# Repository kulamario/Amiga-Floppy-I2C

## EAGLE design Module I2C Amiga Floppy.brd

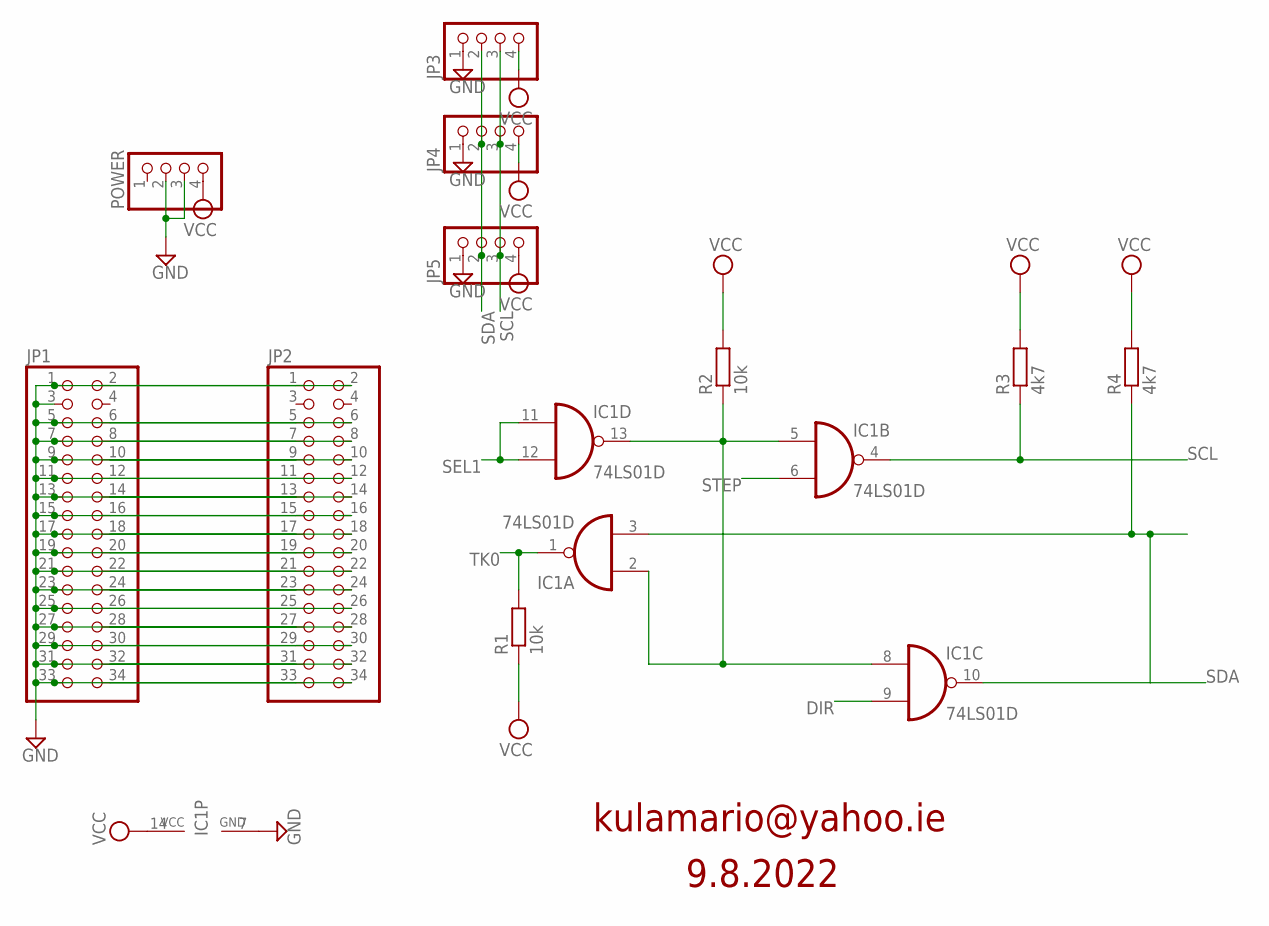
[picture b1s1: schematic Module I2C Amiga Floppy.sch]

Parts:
IC1: 74LS01D; SO14
JP1, JP2: PINHD-2X17; 2X17
JP3, JP4, JP5: PINHD-1X4; 1X04
POWER: PINHD-1X4; 1X04
R1, R2: 10k; R0805
R3, R4: 4k7; R0805

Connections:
DIR: IC1.9 (I1), JP1.18, JP2.18
GND: IC1.7 (GND), JP1.1, JP1.3, JP1.5, JP1.7, JP1.9, JP1.11, JP1.13, JP1.15, JP1.17, JP1.19, JP1.21, JP1.23, JP1.25, JP1.27, JP1.29, JP1.31, JP1.33, JP2.1, JP2.5, JP2.7, JP2.9, JP2.11, JP2.13, JP2.15, JP2.17, JP2.19, JP2.21, JP2.23, JP2.25, JP2.27, JP2.29, JP2.31, JP2.33, JP3.1, JP4.1, JP5.1, POWER.2, POWER.3
unnamed: IC1.2 (I0), IC1.5 (I0), IC1.8 (I0), IC1.13 (O), R2.1
unnamed: JP1.2, JP2.2
unnamed: JP1.6, JP2.6
unnamed: JP1.8, JP2.8
unnamed: JP1.10, JP2.10
unnamed: JP1.14, JP2.14
unnamed: JP1.16, JP2.16
unnamed: JP1.22, JP2.22
unnamed: JP1.24, JP2.24
unnamed: JP1.28, JP2.28
unnamed: JP1.30, JP2.30
unnamed: JP1.32, JP2.32
unnamed: JP1.34, JP2.34
SCL: IC1.4 (O), JP3.3, JP4.3, JP5.3, R3.1
SDA: IC1.3 (I1), IC1.10 (O), JP3.2, JP4.2, JP5.2, R4.1
SEL1: IC1.11 (I0), IC1.12 (I1), JP1.12, JP2.12
STEP: IC1.6 (I1), JP1.20, JP2.20
TK0: IC1.1 (O), JP1.26, JP2.26, R1.2
VCC: IC1.14 (VCC), JP3.4, JP4.4, JP5.4, POWER.4, R1.1, R2.2, R3.2, R4.2

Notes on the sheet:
kulamario@yahoo.ie
9.8.2022

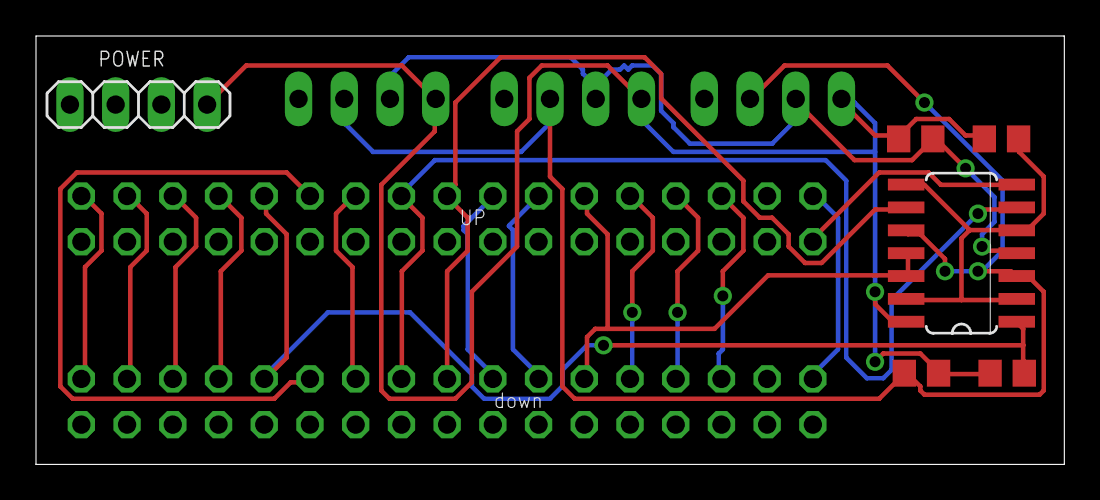
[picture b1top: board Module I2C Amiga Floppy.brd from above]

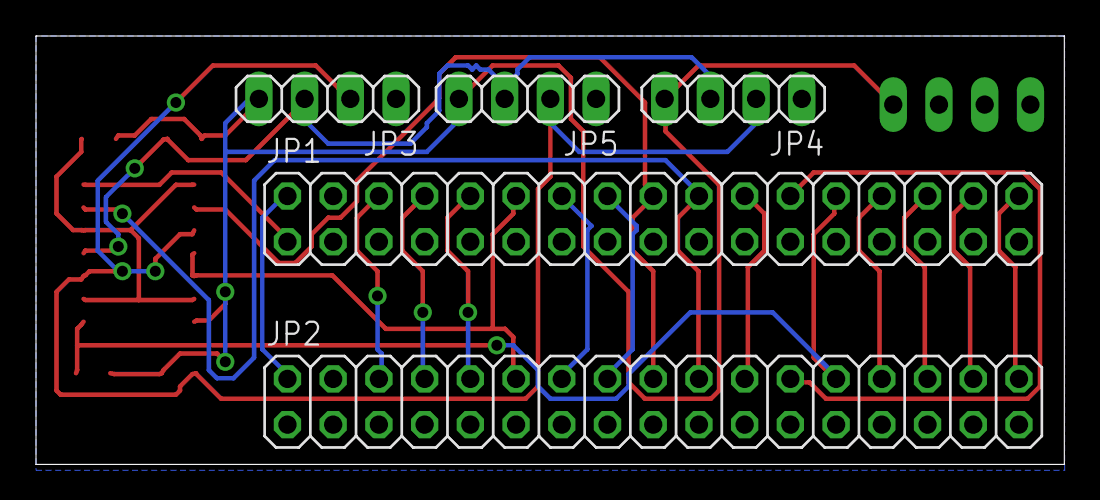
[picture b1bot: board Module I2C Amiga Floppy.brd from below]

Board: 2 copper layers, 57.1 x 23.8 mm, 11 parts (5 on the bottom side), 21 nets.
